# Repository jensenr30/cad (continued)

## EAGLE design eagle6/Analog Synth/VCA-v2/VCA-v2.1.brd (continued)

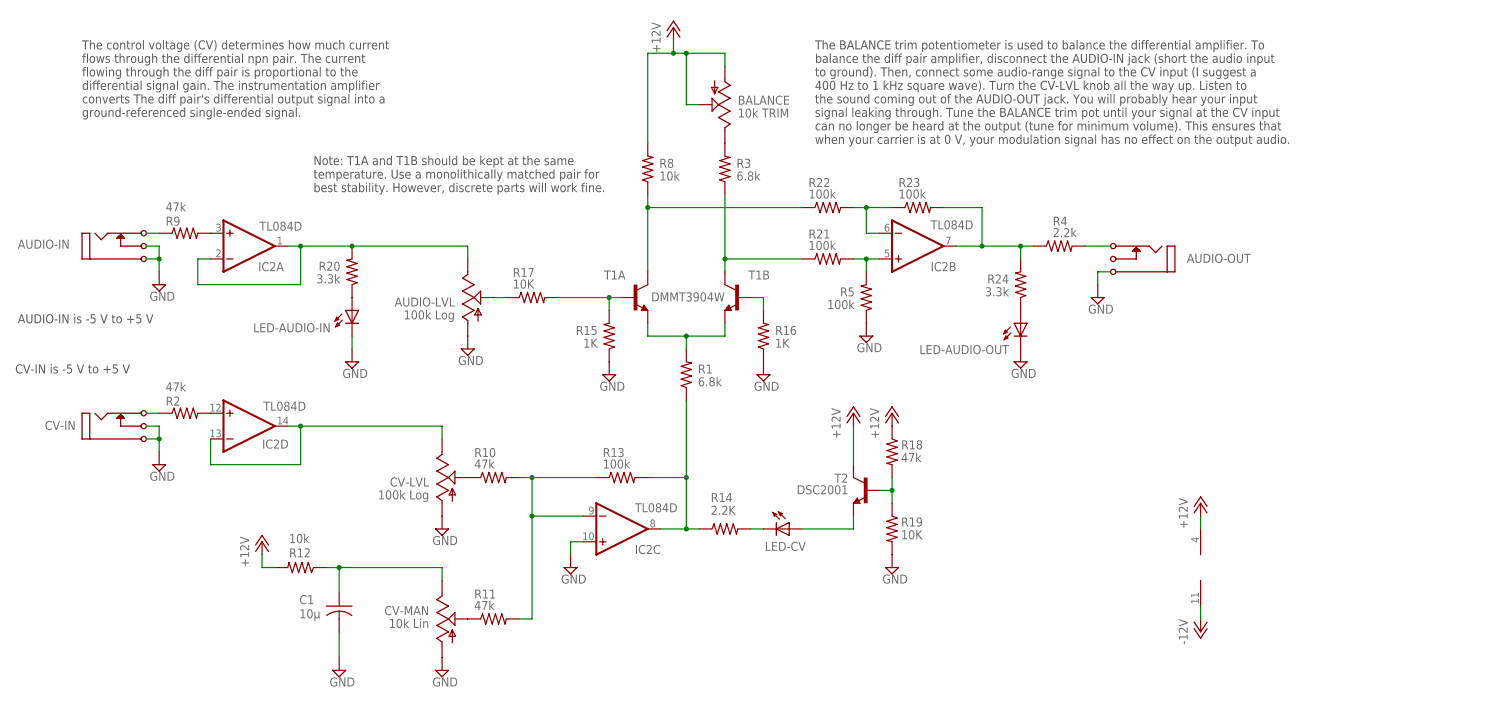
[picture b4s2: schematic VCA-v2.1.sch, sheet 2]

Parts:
AUDIO-IN: I/O; MONO_JACK
AUDIO-LVL: 100k Log; B64Y
AUDIO-OUT: I/O; MONO_JACK
BALANCE: 10k TRIM; B64Y
C1: 10µ; C025-050X050
CV-IN: I/O; MONO_JACK
CV-LVL: 100k Log; B64Y
CV-MAN: 10k Lin; B64Y
IC2: TL084D; SO14
LED-AUDIO-IN: TLLG4400; LED3MM
LED-AUDIO-OUT: TLLG4400; LED3MM
LED-CV: TLLG4400; LED3MM
R1, R3: 6.8k; R0603
R2, R9, R10, R11, R18: 47k; R0603
R4: 2.2k; R0603
R5, R13, R21, R22, R23: 100k; R0603
R8, R12: 10k; R0603
R14: 2.2K; R0603
R15, R16: 1K; R0603
R17, R19: 10K; R0603
R20, R24: 3.3k; R0603
T1: DMMT3904W; SOT363
T2: DSC2001; SOT23-BEC

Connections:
+12V: BALANCE.A, BALANCE.S, IC2.4 (V+), R8.2, R12.2, R18.1, T2.C; also elsewhere on the board
-12V: IC2.11 (V-); also elsewhere on the board
GND: AUDIO-IN.P$1, AUDIO-IN.P$3 (P3), AUDIO-LVL.A, AUDIO-OUT.P$1, C1.2, CV-IN.P$1, CV-IN.P$3 (P3), CV-LVL.A, CV-MAN.A, IC2.10 (+IN), LED-AUDIO-IN.K (C), LED-AUDIO-OUT.K (C), R5.1, R15.1, R16.1, R19.2; also elsewhere on the board
LED_SUPPLY: LED-CV.A, T2.E
unnamed: IC2.8 (OUT), R1.1, R13.2, R14.1
unnamed: BALANCE.E, R3.2
unnamed: IC2.12 (+IN), R2.2
unnamed: CV-LVL.E, IC2.13 (-IN), IC2.14 (OUT)
unnamed: CV-IN.P$2 (P2), R2.1
unnamed: AUDIO-IN.P$2 (P2), R9.1
unnamed: IC2.3 (+IN), R9.2
unnamed: AUDIO-LVL.E, IC2.1 (OUT), IC2.2 (-IN), R20.2
unnamed: CV-LVL.S, R10.1
unnamed: LED-CV.K (C), R14.2
unnamed: CV-MAN.S, R11.1
unnamed: C1.1, CV-MAN.E, R12.1
unnamed: R1.2, T1.4 (E), T1.5 (E)
unnamed: R15.2, R17.2, T1.1 (B)
unnamed: IC2.9 (-IN), R10.2, R11.2, R13.1
unnamed: AUDIO-LVL.S, R17.1
unnamed: R16.2, T1.2 (B)
unnamed: R18.2, R19.1, T2.B
unnamed: LED-AUDIO-IN.A, R20.1
unnamed: LED-AUDIO-OUT.A, R24.1
unnamed: R8.1, R22.1, T1.6 (C)
unnamed: R3.1, R21.1, T1.3 (C)
unnamed: IC2.5 (+IN), R5.2, R21.2
unnamed: IC2.6 (-IN), R22.2, R23.1
unnamed: IC2.7 (OUT), R4.1, R23.2, R24.2
unnamed: AUDIO-OUT.P$2 (P2), R4.2

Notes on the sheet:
The control voltage (CV) determines how much current flows through the differential npn pair. The current flowing through the diff pair is proportional to the differential signal gain. The instrumentation amplifier converts The diff pair's differential output signal into a ground-referenced single-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
The BALANCE trim potentiometer is used to balance the differential amplifier. To balance the diff pair amplifier, disconnect the AUDIO-IN jack (short the audio input to ground). Then, connect some audio-range signal to the CV input (I suggest a 400 Hz to 1 kHz square wave). Turn the CV-LVL knob all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
Note: T1A and T1B should be kept at the same temperature. Use a monolithically matched pair for best stability. However, discrete parts will work fine.
AUDIO-IN is -5 V to +5 V
CV-IN is -5 V to +5 V

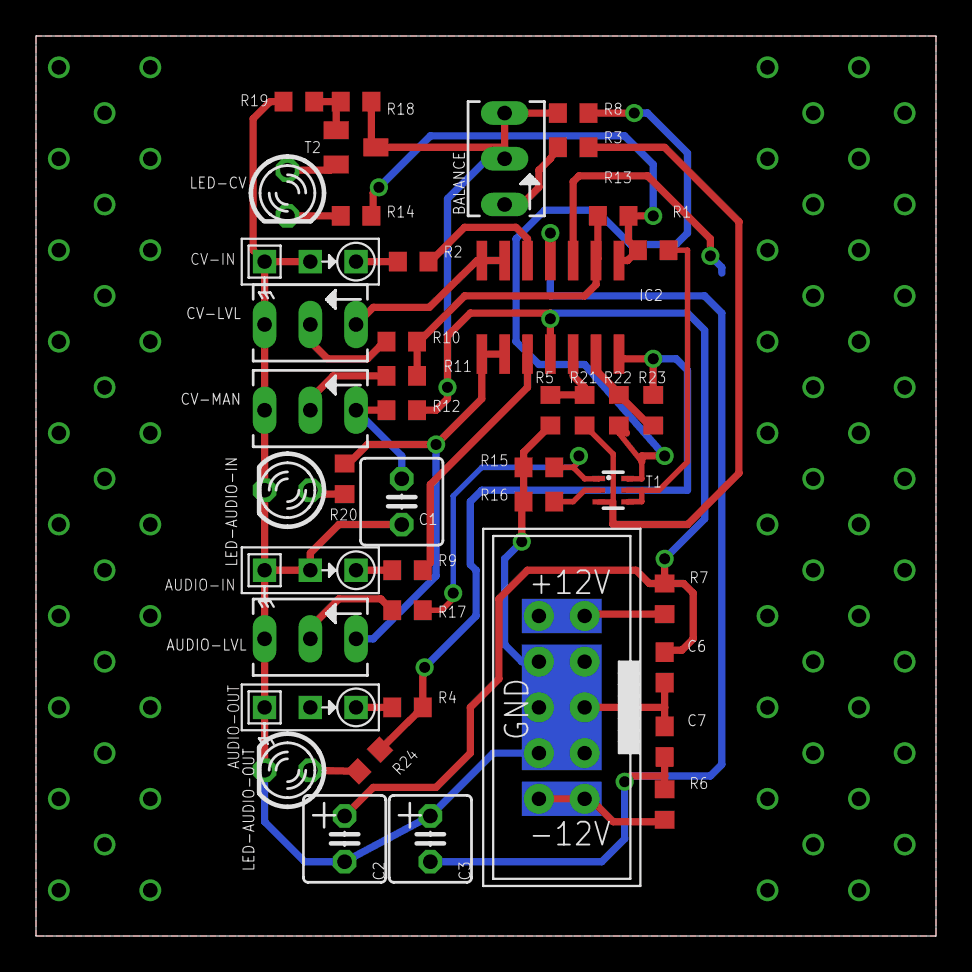
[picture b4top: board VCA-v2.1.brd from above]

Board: 2 copper layers, 50.0 x 50.0 mm, 43 parts (0 on the bottom side), 32 nets.

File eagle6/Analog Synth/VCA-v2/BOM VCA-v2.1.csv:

"Qty","Value","Device","Package","Parts","Description"
"2","0.01µ","C-EUC0603","C0603","C6, C7","CAPACITOR, European symbol"
"5","100k","R-US_R0603","R0603","R5, R13, R21, R22, R23","RESISTOR, American symbol"
"2","100k Log","TRIM_US-B64Y","B64Y","AUDIO-LVL, CV-LVL","POTENTIOMETER"
"2","100µ","C-US025-050X050","C025-050X050","C2, C3","CAPACITOR, American symbol"
"2","10K","R-US_R0603","R0603","R17, R19","RESISTOR, American symbol"
"2","10k","R-US_R0603","R0603","R8, R12","RESISTOR, American symbol"
"1","10k Lin","TRIM_US-B64Y","B64Y","CV-MAN","POTENTIOMETER"
"1","10k TRIM","TRIM_US-B64Y","B64Y","BALANCE","POTENTIOMETER"
"1","10µ","C-US025-050X050","C025-050X050","C1","CAPACITOR, American symbol"
"2","1K","R-US_R0603","R0603","R15, R16","RESISTOR, American symbol"
"1","2.2K","R-US_R0603","R0603","R14","RESISTOR, American symbol"
"1","2.2k","R-US_R0603","R0603","R4","RESISTOR, American symbol"
"2","3.3k","R-US_R0603","R0603","R20, R24","RESISTOR, American symbol"
"5","47k","R-US_R0603","R0603","R2, R9, R10, R11, R18","RESISTOR, American symbol"
"2","6.8k","R-US_R0603","R0603","R1, R3","RESISTOR, American symbol"
"2","7.5","R-US_R0603","R0603","R6, R7","RESISTOR, American symbol"
"1","DMMT3904W","DMMT3904W","SOT363","T1",""
"1","EURORACK-POWER","EURORACK-POWER","EURORACK-POWER","U$1",""
"3","I/O","MONO_JACK","MONO_JACK","AUDIO-IN, AUDIO-OUT, CV-IN",""
"1","DSC2001","DSC2001","SOT23-BEC","T2","NPN Transistror"
"1","TL084D","TL084D","SO14","IC2","OP AMP"
"3","TLLG4400","TLLG4400","LED3MM","LED-AUDIO-IN, LED-AUDIO-OUT, LED-CV","Low Current (2mA) LED 3 mm Tinted Diffused Package color GREEN"

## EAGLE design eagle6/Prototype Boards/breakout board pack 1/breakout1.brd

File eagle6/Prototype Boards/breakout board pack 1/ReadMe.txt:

I don't like how I routed the wires on the bottom for the SOIC-16.
That really sucks. I did not look close enough the first time.

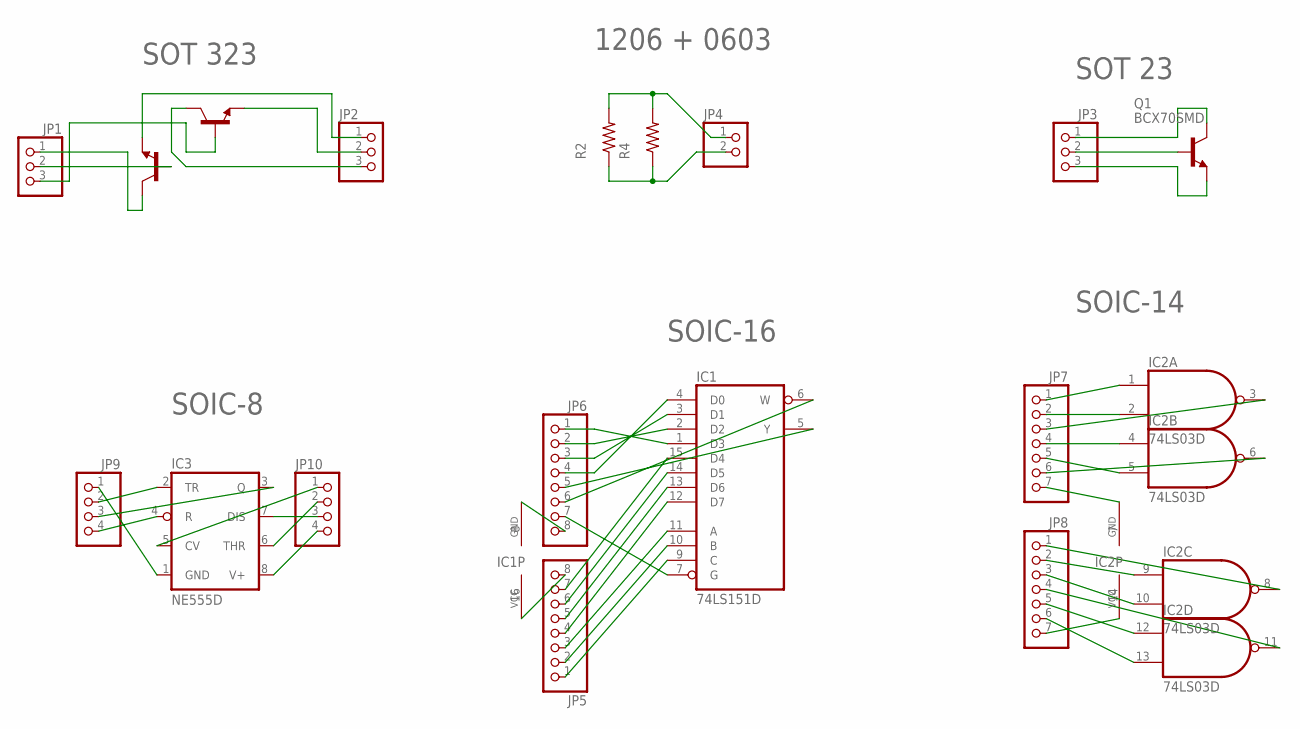
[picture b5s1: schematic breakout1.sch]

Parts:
IC1: 74LS151D; SO16
IC2: 74LS03D; SO14
IC3: NE555D; SO08
JP1, JP2, JP3: PINHD-1X3; 1X03
JP4: PINHD-1X2; 1X02
JP5, JP6: PINHD-1X8; 1X08
JP7, JP8: PINHD-1X7; 1X07
JP9, JP10: PINHD-1X4; 1X04
Q1: BCX70SMD; SOT23
R2: R-US_R0603; R0603
R4: R-US_R1206; R1206
U$1: DMMT3904W; SOT363

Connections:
unnamed: JP1.3, U$1.1 (B)
unnamed: JP1.2, U$1.2 (B)
unnamed: JP1.1, U$1.3 (C)
unnamed: JP2.1, U$1.4 (E)
unnamed: JP2.2, U$1.5 (E)
unnamed: JP2.3, U$1.6 (C)
unnamed: JP3.2, Q1.1 (B)
unnamed: JP3.3, Q1.2 (E)
unnamed: JP4.1, R2.2, R4.2
unnamed: JP4.2, R2.1, R4.1
unnamed: IC1.1 (D3), JP6.1
unnamed: IC1.2 (D2), JP6.2
unnamed: IC1.3 (D1), JP6.3
unnamed: IC1.4 (D0), JP6.4
unnamed: IC1.7 (G), JP6.7
unnamed: IC1.5 (Y), JP6.5
unnamed: IC1.6 (W), JP6.6
unnamed: IC1.8 (GND), JP6.8
unnamed: IC1.9 (C), JP5.1
unnamed: IC1.10 (B), JP5.2
unnamed: IC1.11 (A), JP5.3
unnamed: IC1.12 (D7), JP5.4
unnamed: IC1.13 (D6), JP5.5
unnamed: IC1.14 (D5), JP5.6
unnamed: IC1.15 (D4), JP5.7
unnamed: IC1.16 (VCC), JP5.8
unnamed: IC2.1 (I0), JP7.1
unnamed: IC2.2 (I1), JP7.2
unnamed: IC2.4 (I0), JP7.4
unnamed: IC2.5 (I1), JP7.5
unnamed: IC2.6 (O), JP7.6
unnamed: IC2.3 (O), JP7.3
unnamed: IC2.8 (O), JP8.1
unnamed: IC2.9 (I0), JP8.2
unnamed: IC2.10 (I1), JP8.3
unnamed: IC2.11 (O), JP8.4
unnamed: IC2.12 (I0), JP8.5
unnamed: IC2.13 (I1), JP8.6
unnamed: IC2.14 (VCC), JP8.7
unnamed: IC2.7 (GND), JP7.7
unnamed: IC3.1 (GND), JP9.1
unnamed: IC3.2 (TR), JP9.2
unnamed: IC3.4 (R), JP9.4
unnamed: IC3.3 (Q), JP9.3
unnamed: IC3.5 (CV), JP10.1
unnamed: IC3.6 (THR), JP10.2
unnamed: IC3.7 (DIS), JP10.3
unnamed: IC3.8 (V+), JP10.4
unnamed: JP3.1, Q1.3 (C)

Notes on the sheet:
SOT 323
SOT 23
1206 + 0603
SOIC-16
SOIC-14
SOIC-8

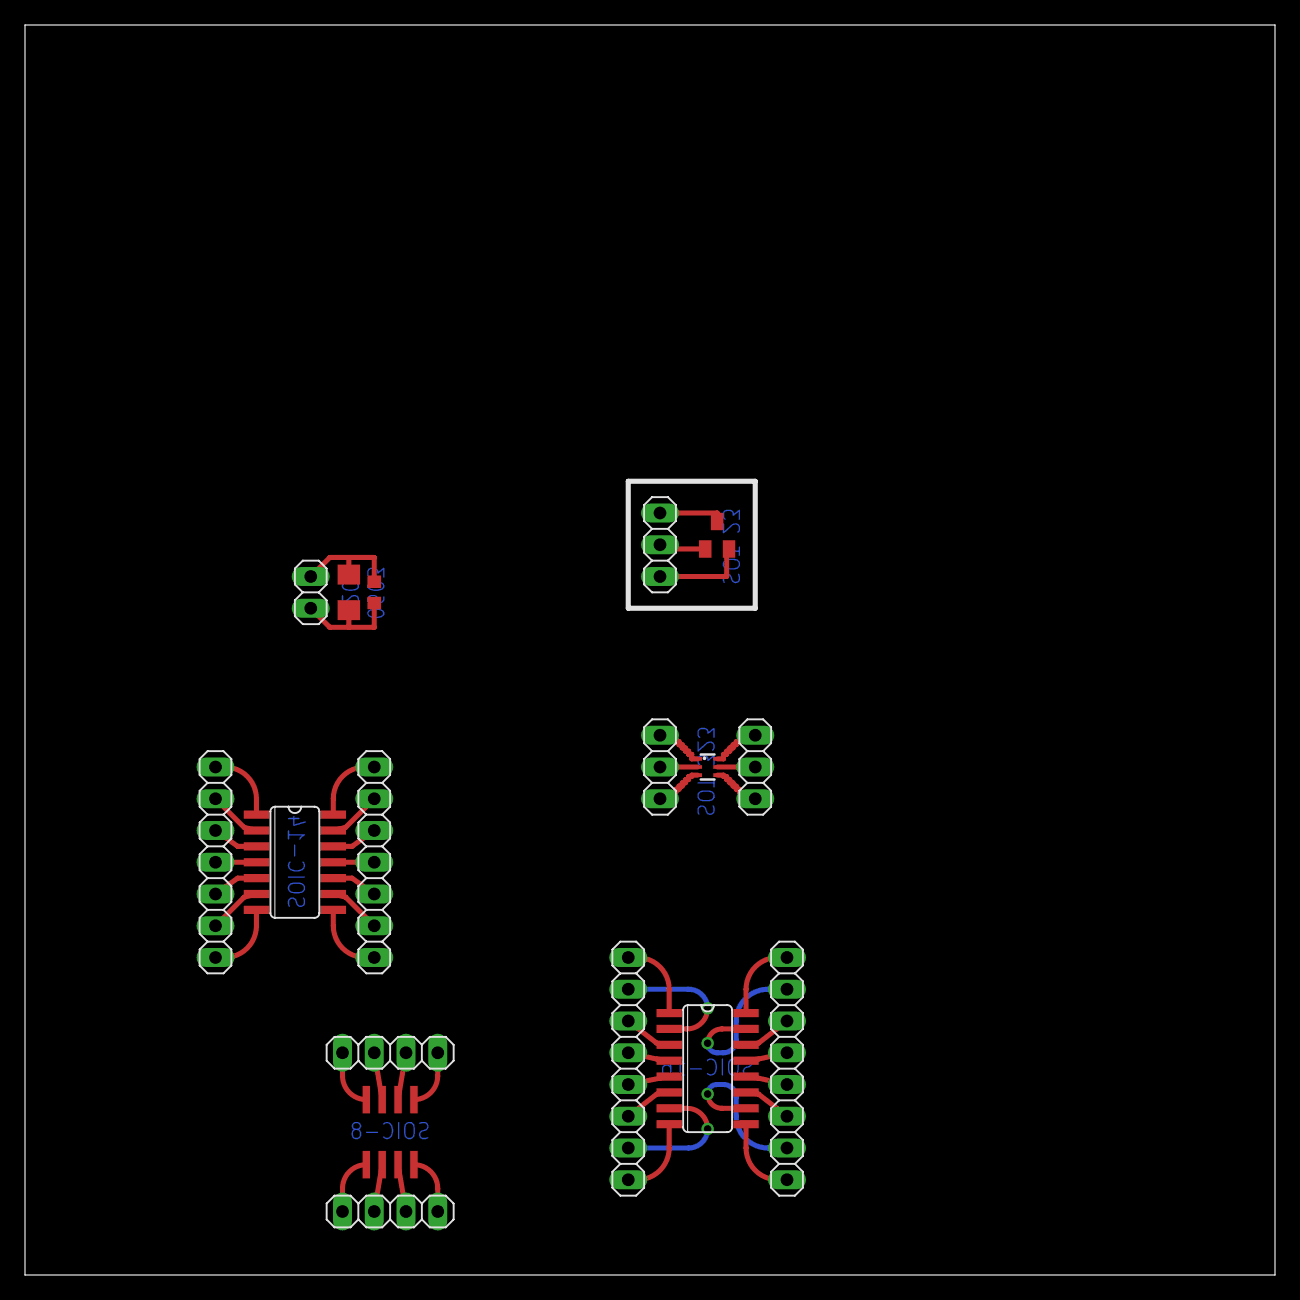
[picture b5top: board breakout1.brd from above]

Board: 2 copper layers, 100.0 x 100.0 mm, 17 parts (0 on the bottom side), 49 nets.

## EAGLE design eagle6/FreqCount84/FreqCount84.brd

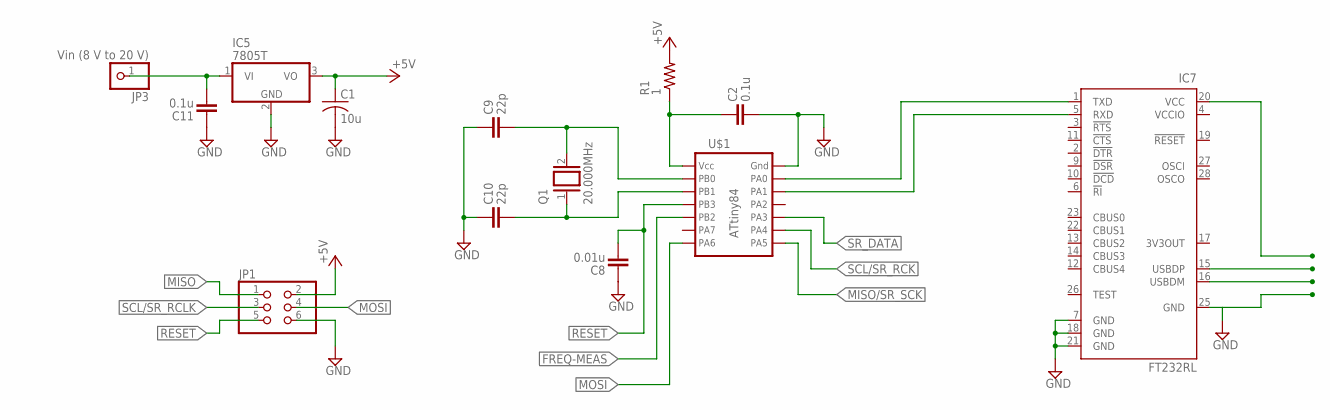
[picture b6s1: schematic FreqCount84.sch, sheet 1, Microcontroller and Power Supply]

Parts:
C1: 10u; C025-050X050
C2, C11: 0.1u; C0603
C8: 0.01u; C0603
C9, C10: 22p; C0603
IC5: 7805T; TO220H
IC7: FT232RL; SSOP28
JP1: PINHD-2X3; 2X03
JP3: Vin (8 V to 20 V); 1X01
Q1: 20.000MHz; QS
R1: 1; R0603
U$1: ATtiny84; SO14

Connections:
+5V: C1.1, IC5.3 (VO), JP1.2, R1.2; also elsewhere on the board
FREQ-MEAS: U$1.5; also elsewhere on the board
GND: C1.2, C2.2, C8.1, C9.1, C10.1, C11.1, IC5.2 (GND), IC7.7 (GND), IC7.18 (GND), IC7.21 (GND), IC7.25 (GND), JP1.6, U$1.14; also elsewhere on the board
MISO: JP1.1
MISO/SR_SCK: U$1.8; also elsewhere on the board
MOSI: JP1.4, U$1.7
unnamed: C9.2, Q1.2, U$1.2
unnamed: C11.2, IC5.1 (VI), JP3.1
unnamed: C2.1, R1.1, U$1.1
unnamed: C10.2, Q1.1, U$1.3
unnamed: IC7.1 (TXD), U$1.13
unnamed: IC7.5 (RXD), U$1.12
RESET: C8.2, JP1.5, U$1.4
SCL/SR_RCK: U$1.9; also elsewhere on the board
SCL/SR_RCLK: JP1.3
SR_DATA: U$1.10; also elsewhere on the board
VCCIO: IC7.4 (VCCIO)

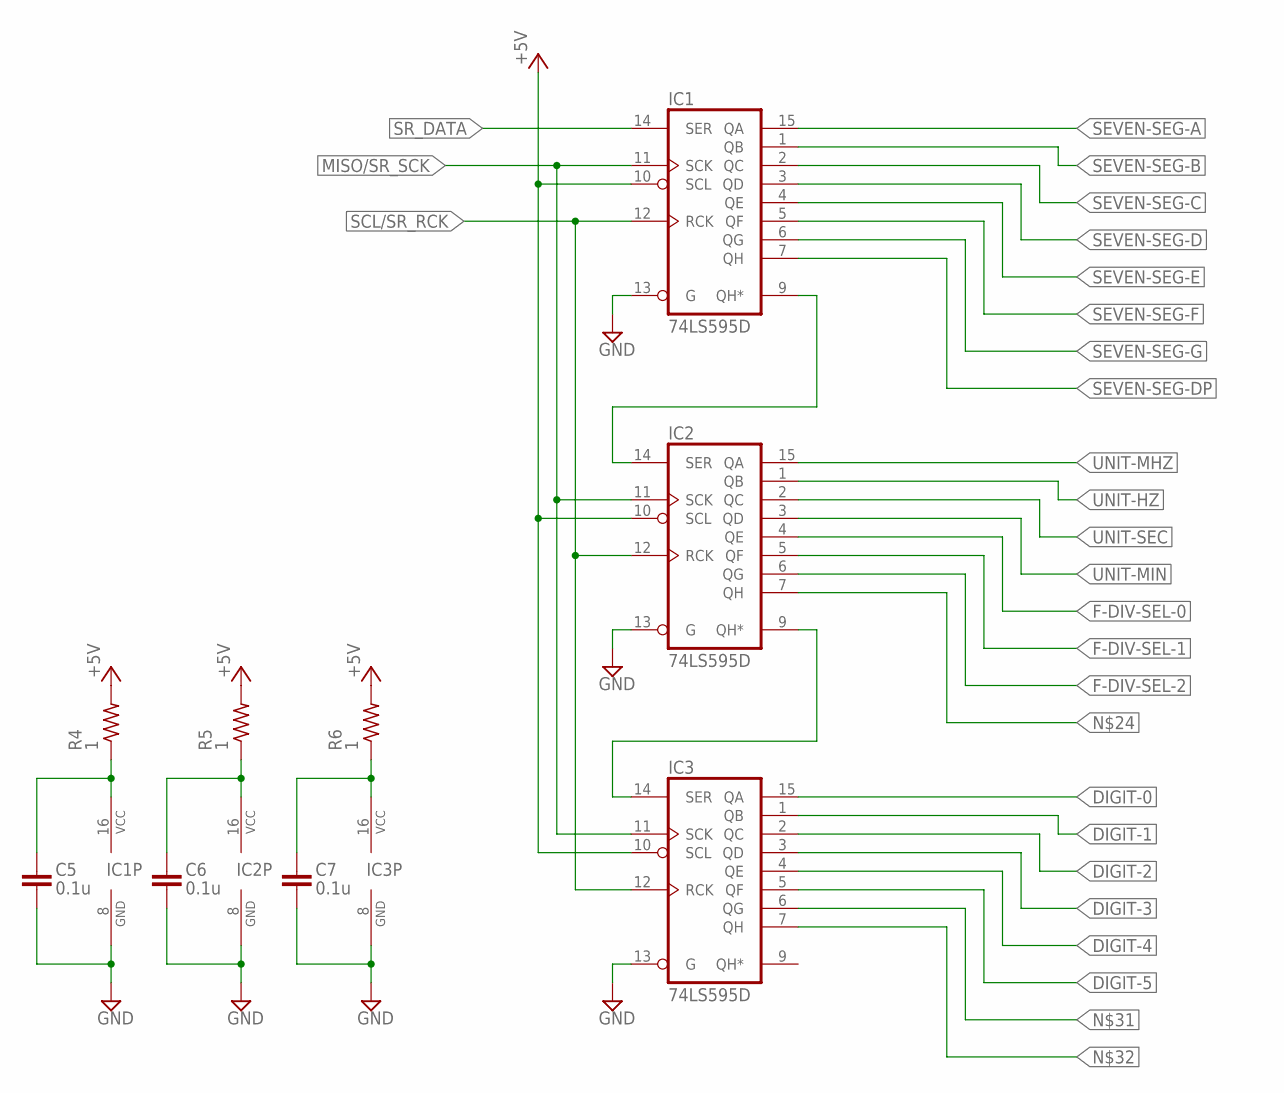
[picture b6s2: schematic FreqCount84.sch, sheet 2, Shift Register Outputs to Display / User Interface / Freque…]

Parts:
C5, C6, C7: 0.1u; C0603
IC1, IC2, IC3: 74LS595D; SO16
R4, R5, R6: 1; R0603

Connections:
+5V: IC1.10 (SCL), IC2.10 (SCL), IC3.10 (SCL), R4.2, R5.2, R6.2; also elsewhere on the board
DIGIT-0: IC3.15 (QA); also elsewhere on the board
DIGIT-1: IC3.1 (QB); also elsewhere on the board
DIGIT-2: IC3.2 (QC); also elsewhere on the board
DIGIT-3: IC3.3 (QD); also elsewhere on the board
DIGIT-4: IC3.4 (QE); also elsewhere on the board
DIGIT-5: IC3.5 (QF); also elsewhere on the board
F-DIV-SEL-0: IC2.4 (QE); also elsewhere on the board
F-DIV-SEL-1: IC2.5 (QF); also elsewhere on the board
F-DIV-SEL-2: IC2.6 (QG); also elsewhere on the board
GND: C5.2, C6.2, C7.2, IC1.8 (GND), IC2.8 (GND), IC2.13 (G), IC3.8 (GND), IC3.13 (G); also elsewhere on the board
MISO/SR_SCK: IC1.11 (SCK), IC2.11 (SCK), IC3.11 (SCK); also elsewhere on the board
unnamed: C5.1, IC1.16 (VCC), R4.1
unnamed: C6.1, IC2.16 (VCC), R5.1
unnamed: IC1.9 (QH*), IC2.14 (SER)
unnamed: IC2.9 (QH*), IC3.14 (SER)
unnamed: C7.1, IC3.16 (VCC), R6.1
SCL/SR_RCK: IC1.12 (RCK), IC2.12 (RCK), IC3.12 (RCK); also elsewhere on the board
SEVEN-SEG-A: IC1.15 (QA); also elsewhere on the board
SEVEN-SEG-B: IC1.1 (QB); also elsewhere on the board
SEVEN-SEG-C: IC1.2 (QC); also elsewhere on the board
SEVEN-SEG-D: IC1.3 (QD); also elsewhere on the board
SEVEN-SEG-DP: IC1.7 (QH)
SEVEN-SEG-E: IC1.4 (QE)
SEVEN-SEG-F: IC1.5 (QF)
SEVEN-SEG-G: IC1.6 (QG)
SR_DATA: IC1.14 (SER); also elsewhere on the board
UNIT-HZ: IC2.1 (QB)
UNIT-MHZ: IC2.15 (QA)
UNIT-MIN: IC2.3 (QD)
UNIT-SEC: IC2.2 (QC)

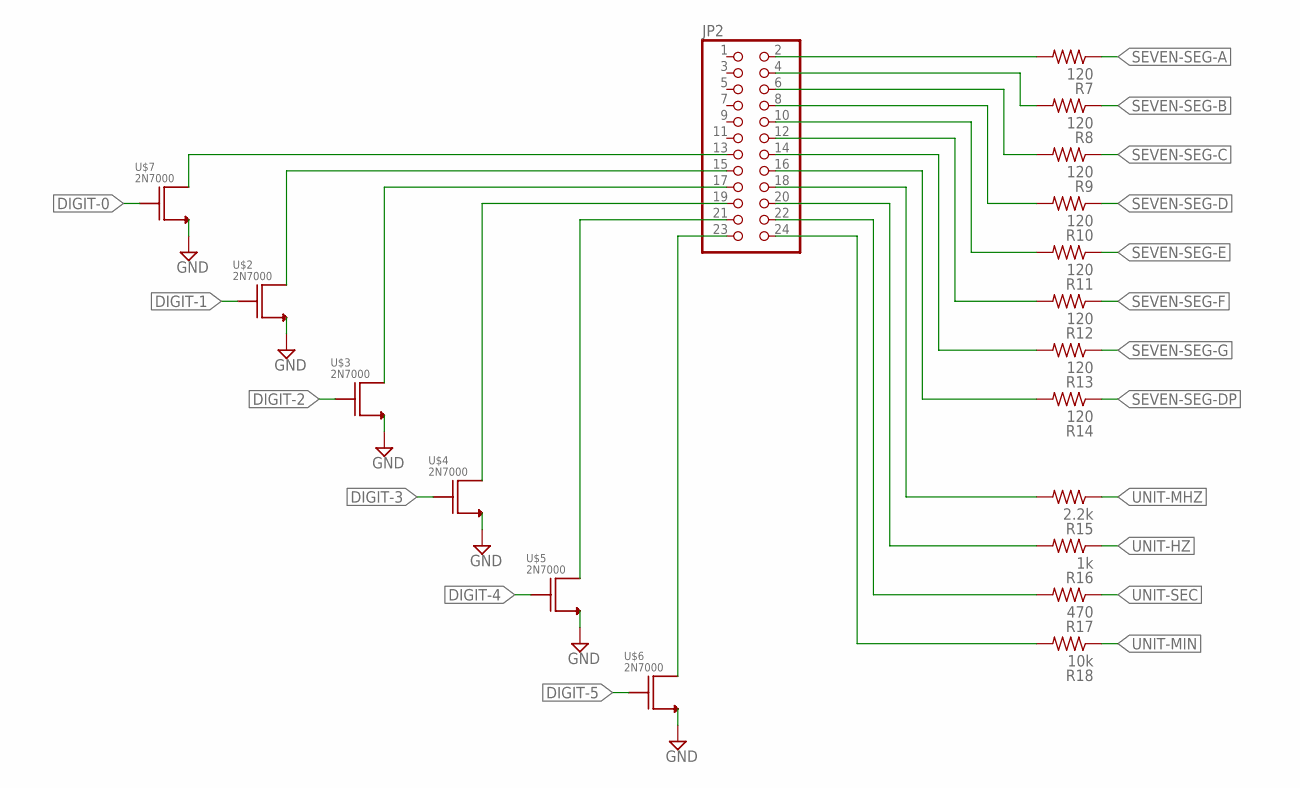
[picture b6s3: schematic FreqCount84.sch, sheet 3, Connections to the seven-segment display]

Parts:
JP2: PINHD-2X12; 2X12
R7, R8, R9, R10, R11, R12, R13, R14: 120; R0603
R15: 2.2k; R0603
R16: 1k; R0603
R17: 470; R0603
R18: 10k; R0603
U$2, U$3, U$4, U$5, U$6, U$7: 2N7000

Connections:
DIGIT-0: U$7.G; also elsewhere on the board
DIGIT-1: U$2.G; also elsewhere on the board
DIGIT-2: U$3.G; also elsewhere on the board
DIGIT-3: U$4.G; also elsewhere on the board
DIGIT-4: U$5.G; also elsewhere on the board
DIGIT-5: U$6.G; also elsewhere on the board
GND: U$2.S, U$3.S, U$4.S, U$5.S, U$6.S, U$7.S; also elsewhere on the board
unnamed: JP2.13, U$7.D
unnamed: JP2.15, U$2.D
unnamed: JP2.17, U$3.D
unnamed: JP2.19, U$4.D
unnamed: JP2.21, U$5.D
unnamed: JP2.23, U$6.D
unnamed: JP2.2, R7.2
unnamed: JP2.4, R8.2
unnamed: JP2.6, R9.2
unnamed: JP2.8, R10.2
unnamed: JP2.10, R11.2
unnamed: JP2.12, R12.2
unnamed: JP2.14, R13.2
unnamed: JP2.16, R14.2
unnamed: JP2.18, R15.2
unnamed: JP2.20, R16.2
unnamed: JP2.22, R17.2
unnamed: JP2.24, R18.2
SEVEN-SEG-A: R7.1; also elsewhere on the board
SEVEN-SEG-B: R8.1; also elsewhere on the board
SEVEN-SEG-C: R9.1; also elsewhere on the board
SEVEN-SEG-D: R10.1; also elsewhere on the board

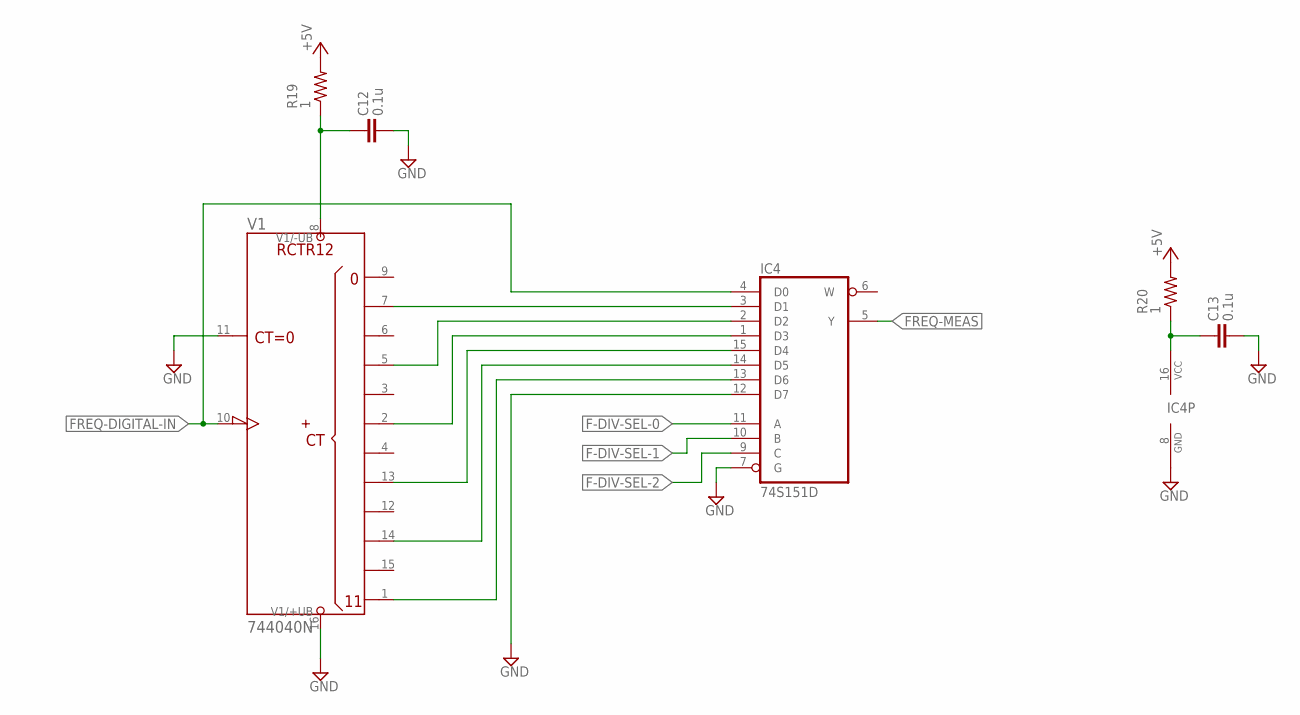
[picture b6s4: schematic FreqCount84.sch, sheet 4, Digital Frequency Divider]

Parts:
C12, C13: 0.1u; C0603
IC4: 74S151D; SO16
R19, R20: 1; R0603
V1: 744040N; DIL16

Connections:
+5V: R19.2, R20.2; also elsewhere on the board
F-DIV-SEL-0: IC4.11 (A); also elsewhere on the board
F-DIV-SEL-1: IC4.10 (B); also elsewhere on the board
F-DIV-SEL-2: IC4.9 (C); also elsewhere on the board
FREQ-DIGITAL-IN: IC4.4 (D0), V1.10 (CLK); also elsewhere on the board
FREQ-MEAS: IC4.5 (Y); also elsewhere on the board
GND: C12.2, C13.2, IC4.7 (G), IC4.8 (GND), IC4.12 (D7), V1.11 (CLR), V1.16 (+UB); also elsewhere on the board
unnamed: IC4.3 (D1), V1.7 (QB)
unnamed: IC4.15 (D4), V1.13 (QH)
unnamed: C12.1, R19.1, V1.8 (-UB)
unnamed: C13.1, IC4.16 (VCC), R20.1
unnamed: IC4.2 (D2), V1.5 (QD)
unnamed: IC4.1 (D3), V1.2 (QF)
unnamed: IC4.14 (D5), V1.14 (QJ)
unnamed: IC4.13 (D6), V1.1 (QL)

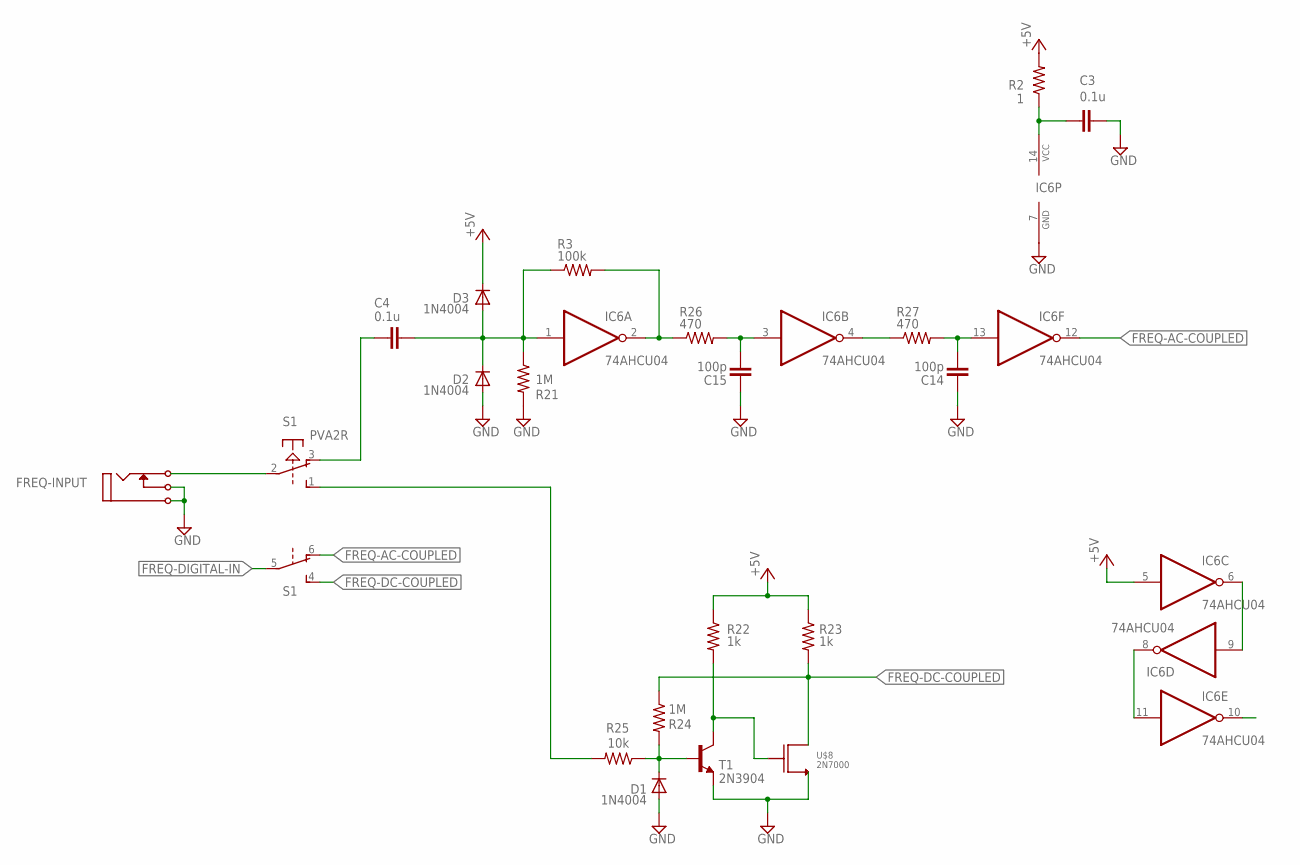
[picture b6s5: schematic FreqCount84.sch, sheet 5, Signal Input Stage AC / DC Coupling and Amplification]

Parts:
C3, C4: 0.1u; C0603
C14, C15: 100p; C0603
D1, D2, D3: 1N4004; DO41-10
FREQ-INPUT: I/O; MONO_JACK
IC6: 74AHCU04; SO14
R2: 1; R0603
R3: 100k; R0603
R21, R24: 1M; R0603
R22, R23: 1k; R0603
R25: 10k; R0603
R26, R27: 470; R0603
S1: PVA2R
T1: 2N3904; TO92
U$8: 2N7000

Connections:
+5V: D3.C, IC6.5 (I), R2.2, R22.1, R23.1; also elsewhere on the board
FREQ-AC-COUPLED: IC6.12 (O), S1.6 (O)
FREQ-DC-COUPLED: R23.2, R24.1, S1.4 (S), U$8.D
FREQ-DIGITAL-IN: S1.5; also elsewhere on the board
GND: C3.2, C14.1, C15.1, D1.A, D2.A, FREQ-INPUT.P$1, FREQ-INPUT.P$3 (P3), IC6.7 (GND), R21.2, T1.3 (E), U$8.S; also elsewhere on the board
unnamed: IC6.2 (O), R3.2, R26.1
unnamed: C15.2, IC6.3 (I), R26.2
unnamed: C14.2, IC6.13 (I), R27.2
unnamed: IC6.4 (O), R27.1
unnamed: IC6.6 (O), IC6.9 (I)
unnamed: C3.1, IC6.14 (VCC), R2.1
unnamed: R22.2, T1.1 (C), U$8.G
unnamed: C4.1, S1.3 (O)
unnamed: IC6.8 (O), IC6.11 (I)
unnamed: R25.2, S1.1 (S)
unnamed: FREQ-INPUT.P$2 (P2), S1.2
unnamed: C4.2, D2.C, D3.A, IC6.1 (I), R3.1, R21.1
unnamed: D1.C, R24.2, R25.1, T1.2 (B)

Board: 2 copper layers, 68 parts (0 on the bottom side), 74 nets, no tracks yet.

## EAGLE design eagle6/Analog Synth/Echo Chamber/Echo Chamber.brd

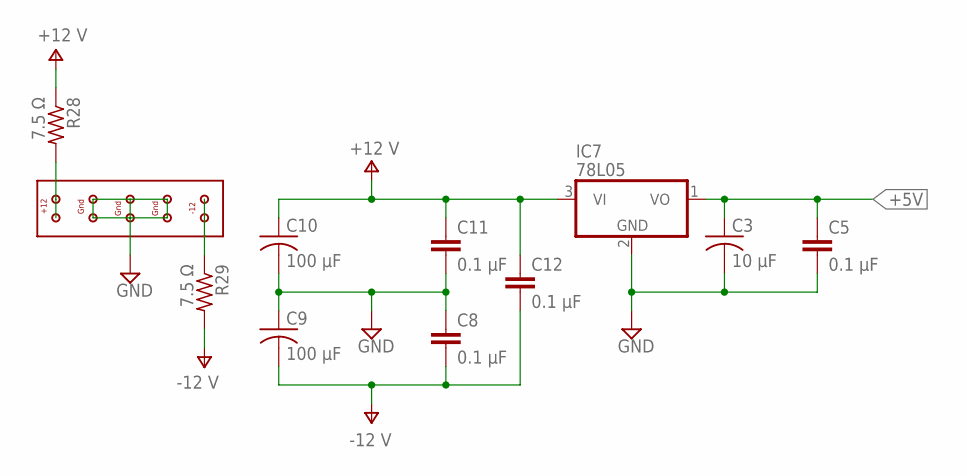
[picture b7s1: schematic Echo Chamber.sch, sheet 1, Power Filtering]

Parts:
C3: 10 µF; C025-060X050
C5, C8, C11, C12: 0.1 µF; C5B2.5
C9, C10: 100 µF; C025-060X050
IC7: 78L05; TO92
R28, R29: 7.5 Ω; 0204/7
U$2: EURORACK-POWER

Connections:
+5V: C3.1, C5.1, IC7.1 (VO); also elsewhere on the board
GND: C3.2, C5.2, C8.1, C9.1, C10.2, C11.2, IC7.2 (GND), U$2.P$3, U$2.P$4, U$2.P$5, U$2.P$6, U$2.P$7, U$2.P$8; also elsewhere on the board
unnamed: R29.1, U$2.P$9, U$2.P$10
unnamed: R28.2, U$2.P$1, U$2.P$2
V+: C10.1, C11.1, C12.1, IC7.3 (VI), R28.1; also elsewhere on the board
V-: C8.2, C9.2, C12.2, R29.2; also elsewhere on the board

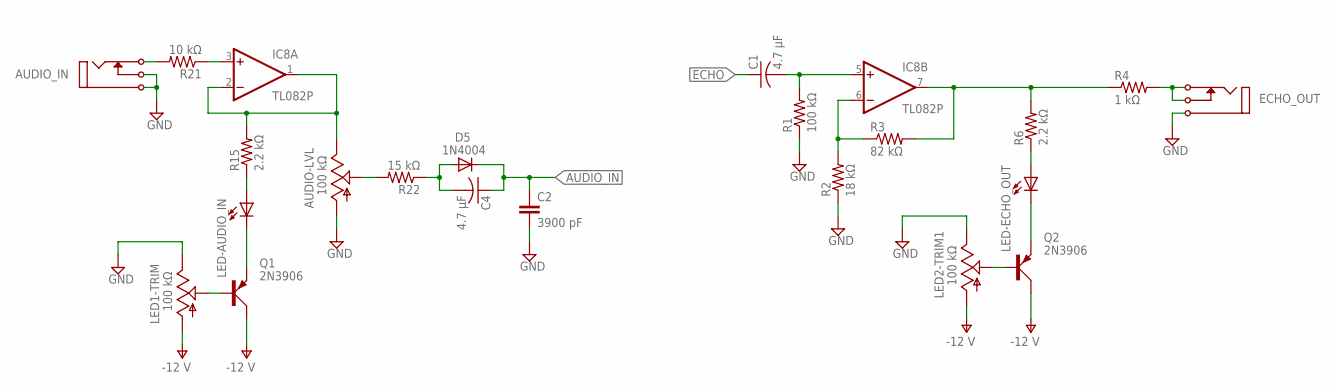
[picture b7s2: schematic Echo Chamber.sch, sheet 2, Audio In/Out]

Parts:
AUDIO-LVL: 100 kΩ; B64Y
AUDIO_IN: I/O; MONO_JACK
C1, C4: 4.7 µF; C025-060X050
C2: 3900 pF; C5B2.5
D5: 1N4004; DO41-10
ECHO_OUT: I/O; MONO_JACK
IC8: TL082P; DIL08
LED1-TRIM, LED2-TRIM1: 100 kΩ; B64Y
LED-AUDIO_IN: LED3MM
LED-ECHO_OUT: LED3MM
Q1, Q2: 2N3906; TO92D
R1: 100 kΩ; 0204/7
R2: 18 kΩ; 0204/7
R3: 82 kΩ; 0204/7
R4: 1 kΩ; 0204/7
R6, R15: 2.2 kΩ; 0204/7
R21: 10 kΩ; 0204/7
R22: 15 kΩ; 0204/7

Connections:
AUDIO_IN: C2.1, C4.1, D5.C; also elsewhere on the board
CV-A: AUDIO-LVL.E, IC8.1 (OUT), IC8.2 (-IN), R15.2
ECHO: C1.1; also elsewhere on the board
GND: AUDIO-LVL.A, AUDIO_IN.P$1, AUDIO_IN.P$3 (P3), C2.2, ECHO_OUT.P$1, LED1-TRIM.E, LED2-TRIM1.E, R1.1, R2.1; also elsewhere on the board
unnamed: C1.2, IC8.5 (+IN), R1.2
unnamed: IC8.6 (-IN), R2.2, R3.1
unnamed: IC8.7 (OUT), R3.2, R4.1, R6.2
unnamed: LED-AUDIO_IN.K (C), Q1.E
unnamed: ECHO_OUT.P$2 (P2), ECHO_OUT.P$3 (P3), R4.2
unnamed: IC8.3 (+IN), R21.1
unnamed: AUDIO_IN.P$2 (P2), R21.2
unnamed: AUDIO-LVL.S, R22.2
unnamed: LED-ECHO_OUT.K (C), Q2.E
unnamed: LED-AUDIO_IN.A, R15.1
unnamed: LED-ECHO_OUT.A, R6.1
unnamed: LED2-TRIM1.S, Q2.B
unnamed: C4.2, D5.A, R22.1
unnamed: LED1-TRIM.S, Q1.B
V+: IC8.8 (V+); also elsewhere on the board
V-: IC8.4 (V-), LED1-TRIM.A, LED2-TRIM1.A, Q2.C; also elsewhere on the board

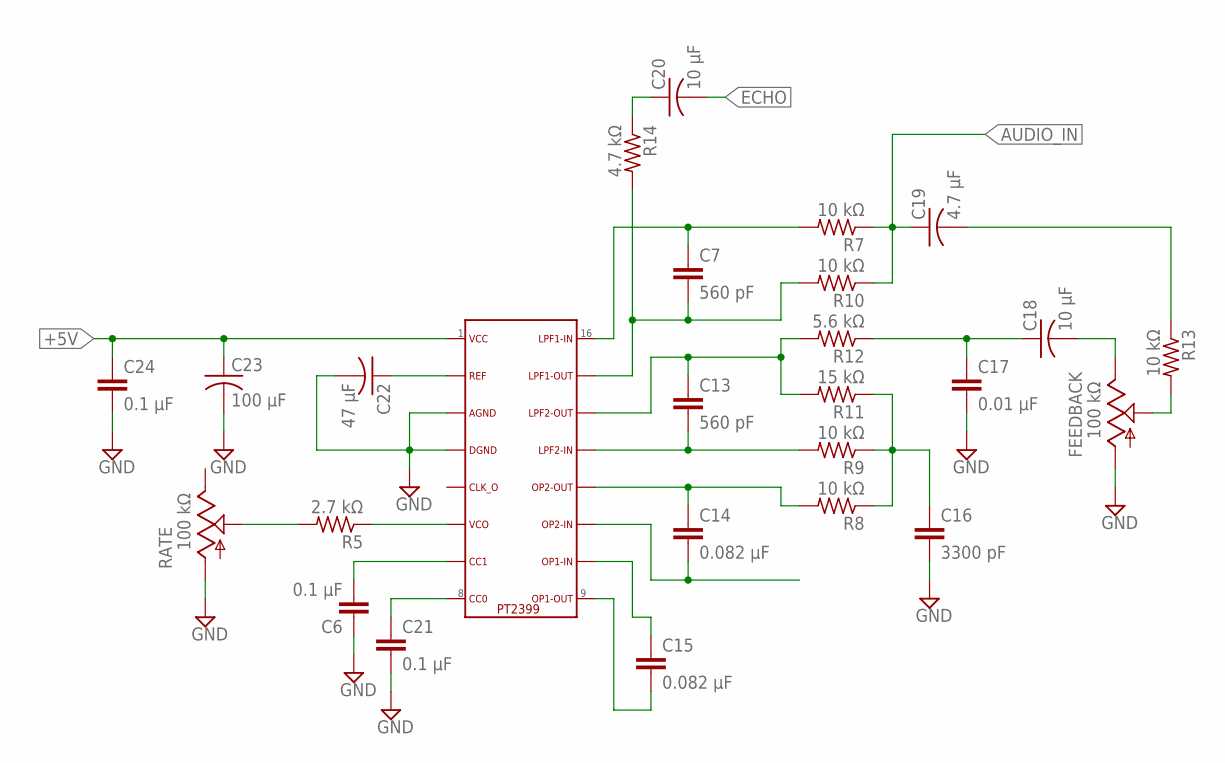
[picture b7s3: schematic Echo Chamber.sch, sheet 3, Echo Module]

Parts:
C6, C21, C24: 0.1 µF; C5B2.5
C7, C13: 560 pF; C5B2.5
C14, C15: 0.082 µF; C5B2.5
C16: 3300 pF; C5B2.5
C17: 0.01 µF; C5B2.5
C18, C20: 10 µF; C025-060X050
C19: 4.7 µF; C025-060X050
C22: 47 µF; C025-060X050
C23: 100 µF; C025-060X050
FEEDBACK: 100 kΩ; B64Y
R5: 2.7 kΩ; 0204/7
R7, R8, R9, R10, R13: 10 kΩ; 0204/7
R11: 15 kΩ; 0204/7
R12: 5.6 kΩ; 0204/7
R14: 4.7 kΩ; 0204/7
RATE: 100 kΩ; B64Y
U$1: PT2399

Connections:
+5V: C23.1, C24.1, U$1.1; also elsewhere on the board
AUDIO_IN: C19.1, R7.1, R10.1; also elsewhere on the board
ECHO: C20.2; also elsewhere on the board
GND: C6.1, C16.2, C17.2, C21.2, C22.2, C23.2, C24.2, FEEDBACK.A, RATE.A, U$1.3, U$1.4; also elsewhere on the board
unnamed: C7.1, R7.2, U$1.16
unnamed: C7.2, R10.2, R14.2, U$1.15
unnamed: C13.2, R9.2, U$1.13
unnamed: C14.1, R8.2, U$1.12
unnamed: C17.1, C18.1, R12.1
unnamed: C14.2, U$1.11
unnamed: C15.1, U$1.10
unnamed: C15.2, U$1.9
unnamed: C16.1, R8.1, R9.1, R11.1
unnamed: C20.1, R14.1
unnamed: C13.1, R11.2, R12.2, U$1.14
unnamed: C18.2, FEEDBACK.E
unnamed: FEEDBACK.S, R13.2
unnamed: C19.2, R13.1
unnamed: C6.2, U$1.7
unnamed: C21.1, U$1.8
unnamed: R5.1, U$1.6
unnamed: R5.2, RATE.S
unnamed: C22.1, U$1.2

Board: 2 copper layers, 59 parts (0 on the bottom side), 42 nets, no tracks yet.
